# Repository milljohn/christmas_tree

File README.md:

# LED Christmas Tree

Give the gift of hacking. This is a great project to learn how to program or just enjoy the existing sketch.

## Background
I originally made this for my daughters when they were part of a community group for young entrepreneurs. The LED Christmas Tree was designed to be a product for them to build and sell. ThreeGirlsMakeStuff is now defunct.

## Programming

Supplies:
- [SparkFun ISP Pogo Adapter](https://www.sparkfun.com/products/11591)
- [USB Tiny AVR](https://www.aliexpress.com/item/1005003257284683.html?spm=a2g0o.productlist.0.0.764f665euosCDP&algo_pvid=e8b9d653-d5cf-4580-b718-6405428d7faf&algo_exp_id=e8b9d653-d5cf-4580-b718-6405428d7faf-10&pdp_ext_f=%7B%22sku_id%22%3A%2212000024884249441%22%7D)

The easiest thing to do is solder the Tiny AVR to the ISP Pogo Adapter.

- Click on File>Preferences 
- Add this to Additional Boards Manager URLs: ``https://raw.githubusercontent.com/damellis/attiny/ide-1.6.x-boards-manager/package_damellis_attiny_index.json`` 
- Click on Tools>Board>Board Manager
- Search for `attiny85` and install 
- Select ``ATtiny85``, ``Internal 8MHz``
- Click on Sketch>Include Library>Library Manager
- Search for Neopixel 

You can use any of the NeoPixel example sketches. Use the following configuration.

````c
#include <Adafruit_NeoPixel.h>
#ifdef __AVR__
  #include <avr/power.h>
#endif

#define PIN 0
#define NUM_LEDS 10
#define BRIGHTNESS 15

Adafruit_NeoPixel strip = Adafruit_NeoPixel(NUM_LEDS, PIN, NEO_GRB + NEO_KHZ800);
```

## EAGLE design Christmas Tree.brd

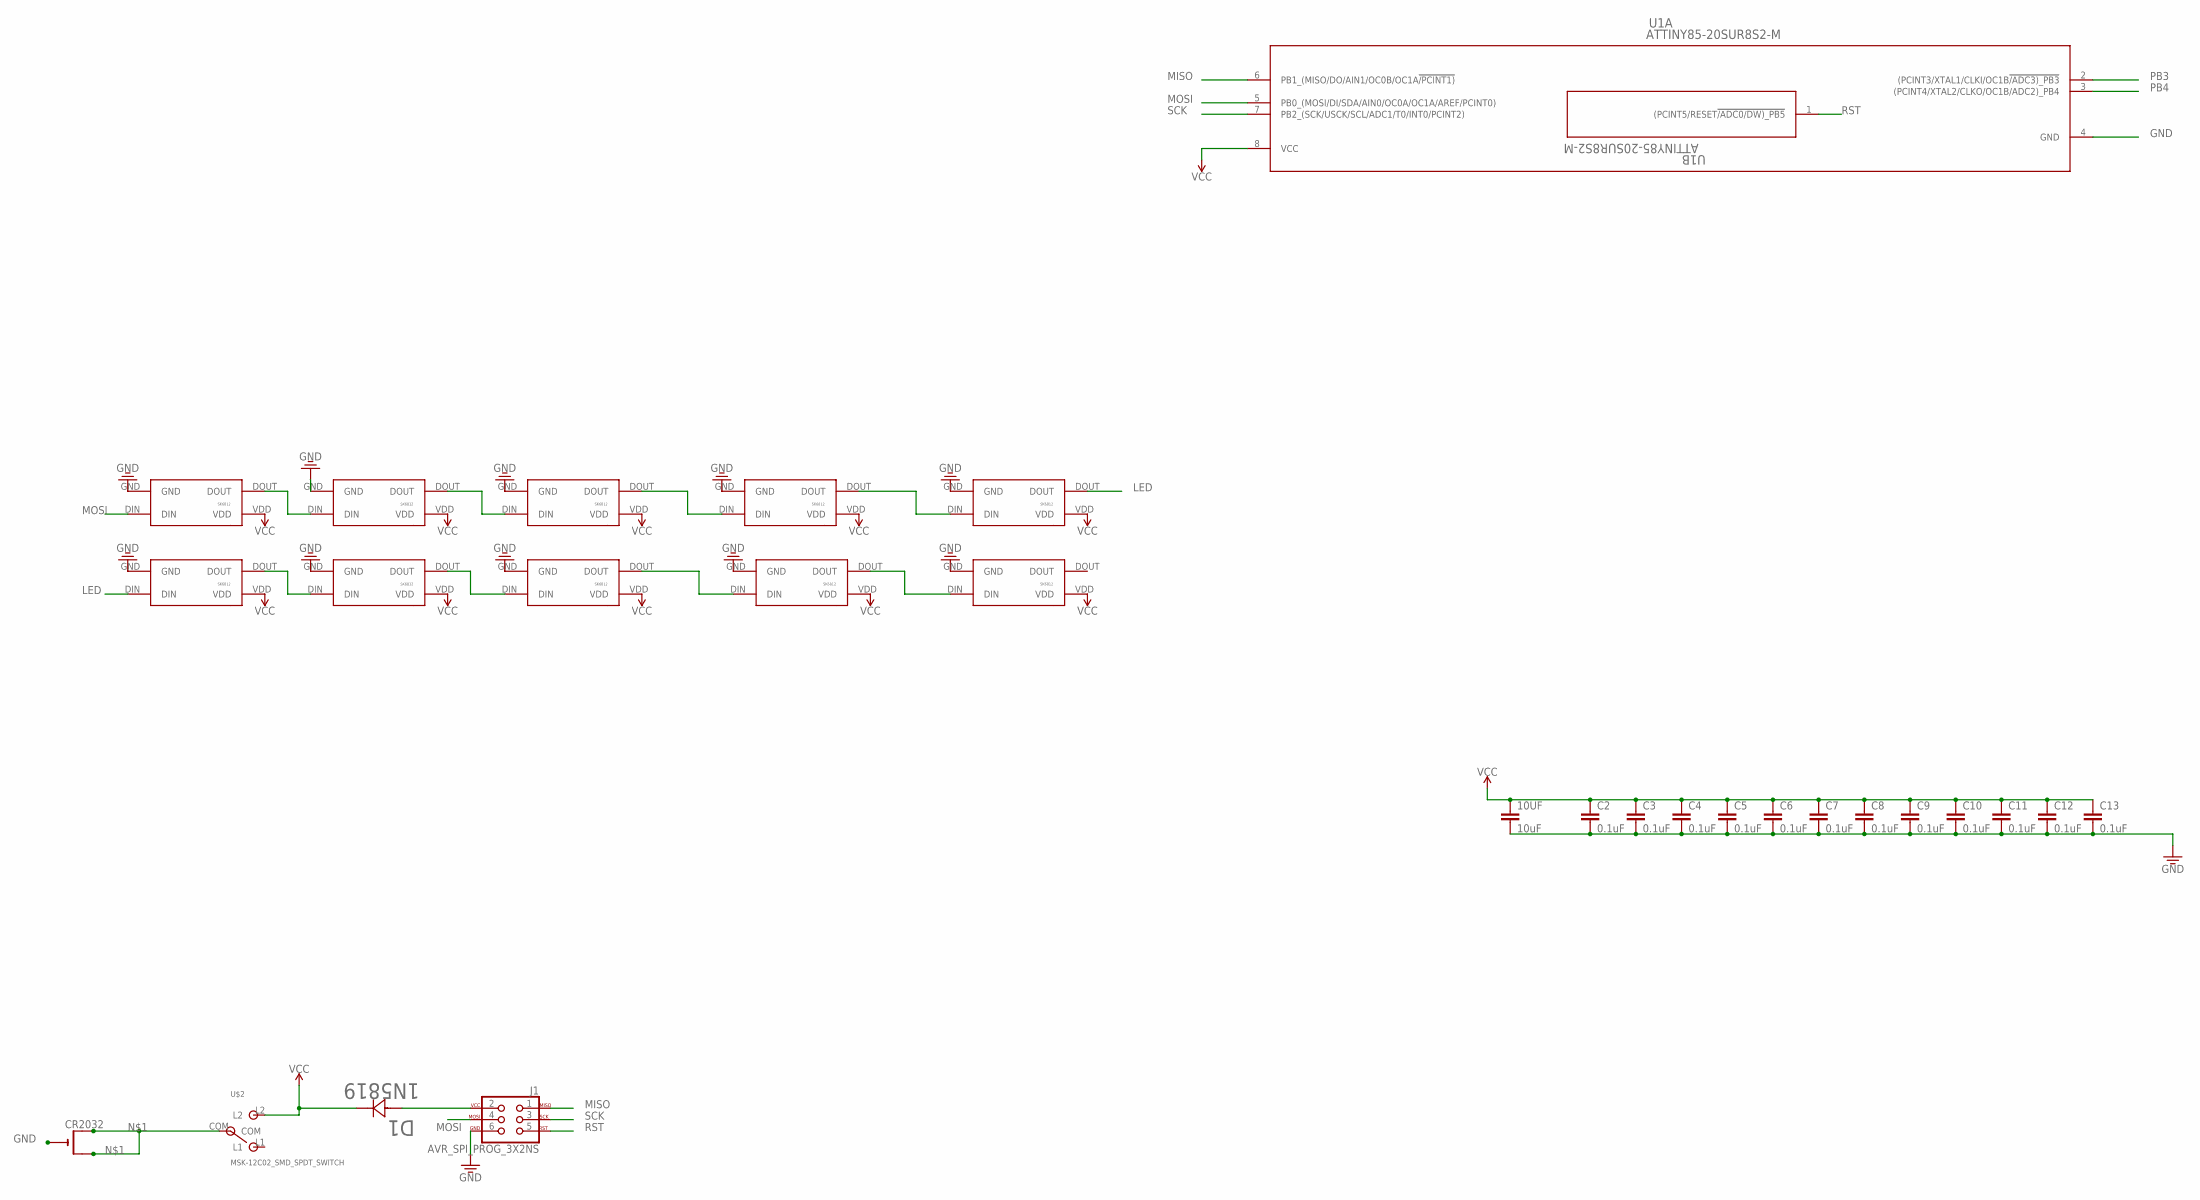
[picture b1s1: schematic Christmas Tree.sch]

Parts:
10UF: 10uF; 0805
C2, C3, C4, C5, C6, C7, C8, C9, C10, C11, C12, C13: 0.1uF; 0805
CR2032: CR2032SMT; CR2032-SMD
D1: 1N5819; SOD123-M
J1: AVR_SPI_PROG_3X2NS; 2X3-NS
U1: ATTINY85-20SUR8S2-M; 8S2-M
U$2: MSK-12C02_SMD_SPDT_SWITCH; MSK-12C02
U$3, U$4, U$5, U$6, U$7, U$8, U$9, U$10, U$11, U$12: SK6812; 5050

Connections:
GND: 10UF.2, C2.2, C3.2, C4.2, C5.2, C6.2, C7.2, C8.2, C9.2, C10.2, C11.2, C12.2, C13.2, CR2032.-, J1.6, U1.4 (GND), U$3.GND, U$4.GND, U$5.GND, U$6.GND, U$7.GND, U$8.GND, U$9.GND, U$10.GND, U$11.GND, U$12.GND
LED: U$7.DOUT, U$8.DIN
MISO: J1.1, U1.6 (PB1_(MISO/DO/AIN1/OC0B/OC1A!/PCINT1))
MOSI: J1.4, U1.5 (PB0_(MOSI/DI/SDA/AIN0/OC0A/OC1A/AREF/PC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), U$3.DIN
unnamed: CR2032.+$1 (+), CR2032.+$2 (+1), U$2.COM
unnamed: U$4.DOUT, U$5.DIN
unnamed: U$5.DOUT, U$6.DIN
unnamed: U$6.DOUT, U$7.DIN
unnamed: U$9.DOUT, U$10.DIN
unnamed: U$8.DOUT, U$9.DIN
unnamed: U$10.DOUT, U$11.DIN
unnamed: U$11.DOUT, U$12.DIN
unnamed: U$3.DOUT, U$4.DIN
unnamed: D1.2 (21), J1.2
PB3: U1.2 ((PCINT3/XTAL1/CLKI/OC1B!/ADC3)_PB3)
PB4: U1.3 ((PCINT4/XTAL2/CLKO/OC1B/ADC2)_PB4)
RST: J1.5, U1.1 ((PCINT5/RESET!/ADC0/DW)_PB5)
SCK: J1.3, U1.7 (PB2_(SCK/USCK/SCL/ADC1/T0/INT0/PCINT2))
VCC: 10UF.1, C2.1, C3.1, C4.1, C5.1, C6.1, C7.1, C8.1, C9.1, C10.1, C11.1, C12.1, C13.1, D1.1 (12), U1.8 (VCC), U$2.L2, U$3.VDD, U$4.VDD, U$5.VDD, U$6.VDD, U$7.VDD, U$8.VDD, U$9.VDD, U$10.VDD, U$11.VDD, U$12.VDD

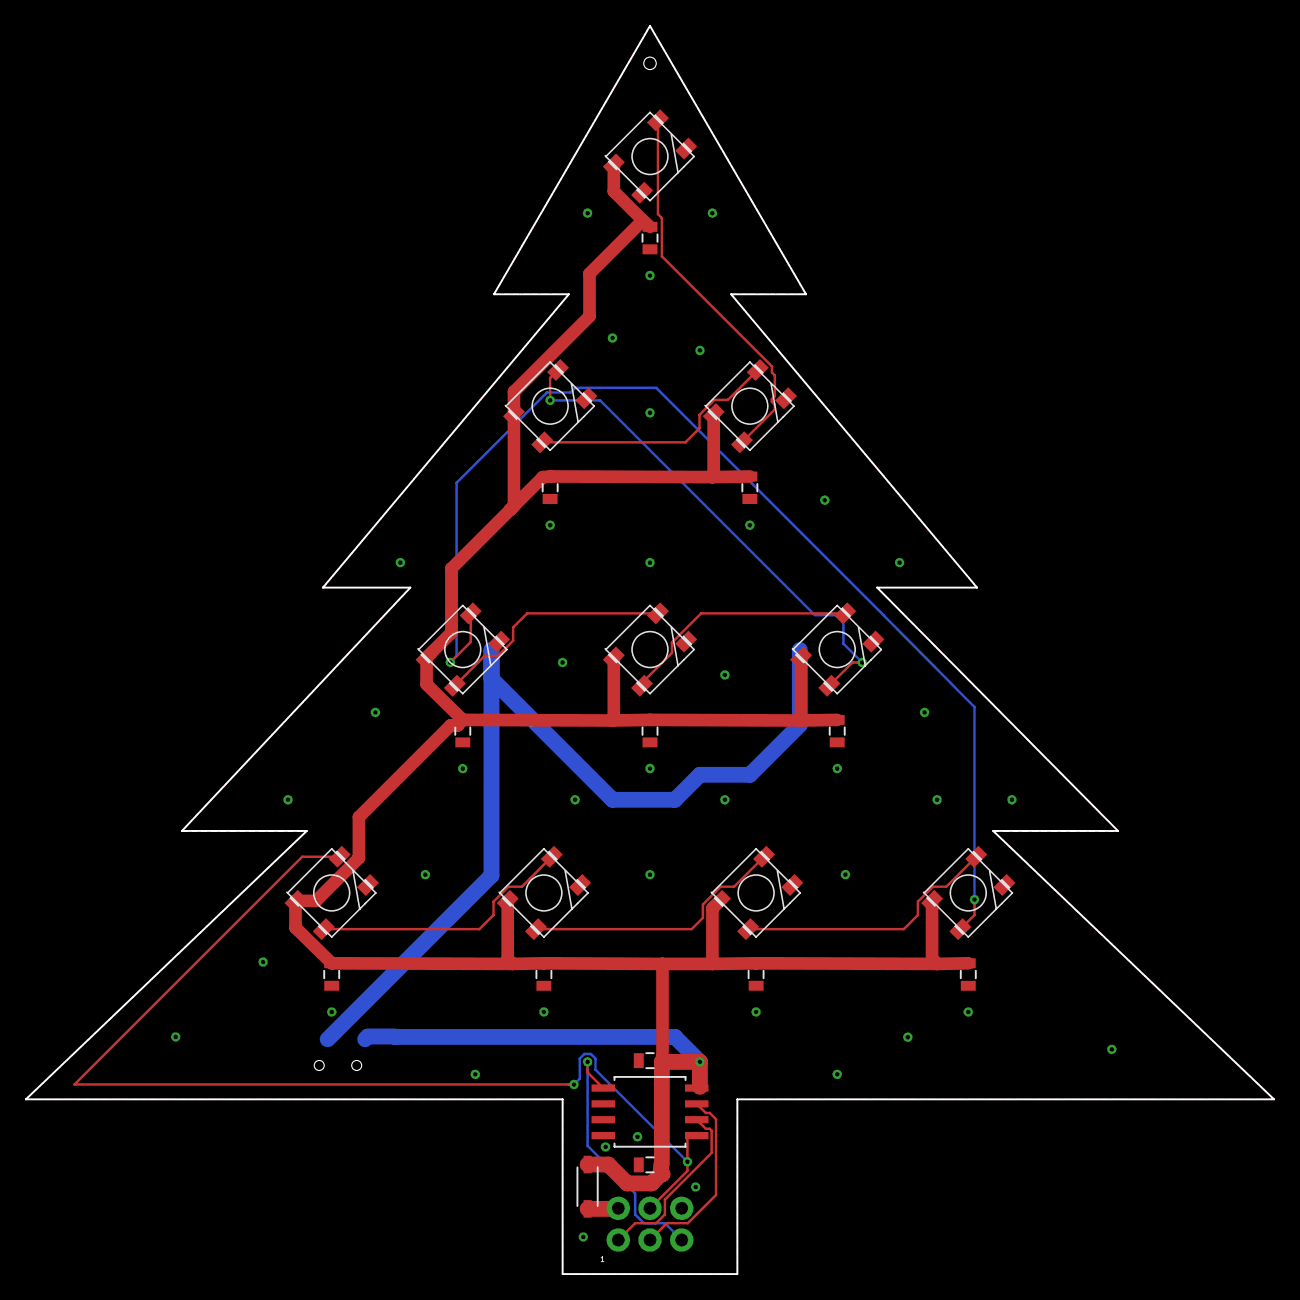
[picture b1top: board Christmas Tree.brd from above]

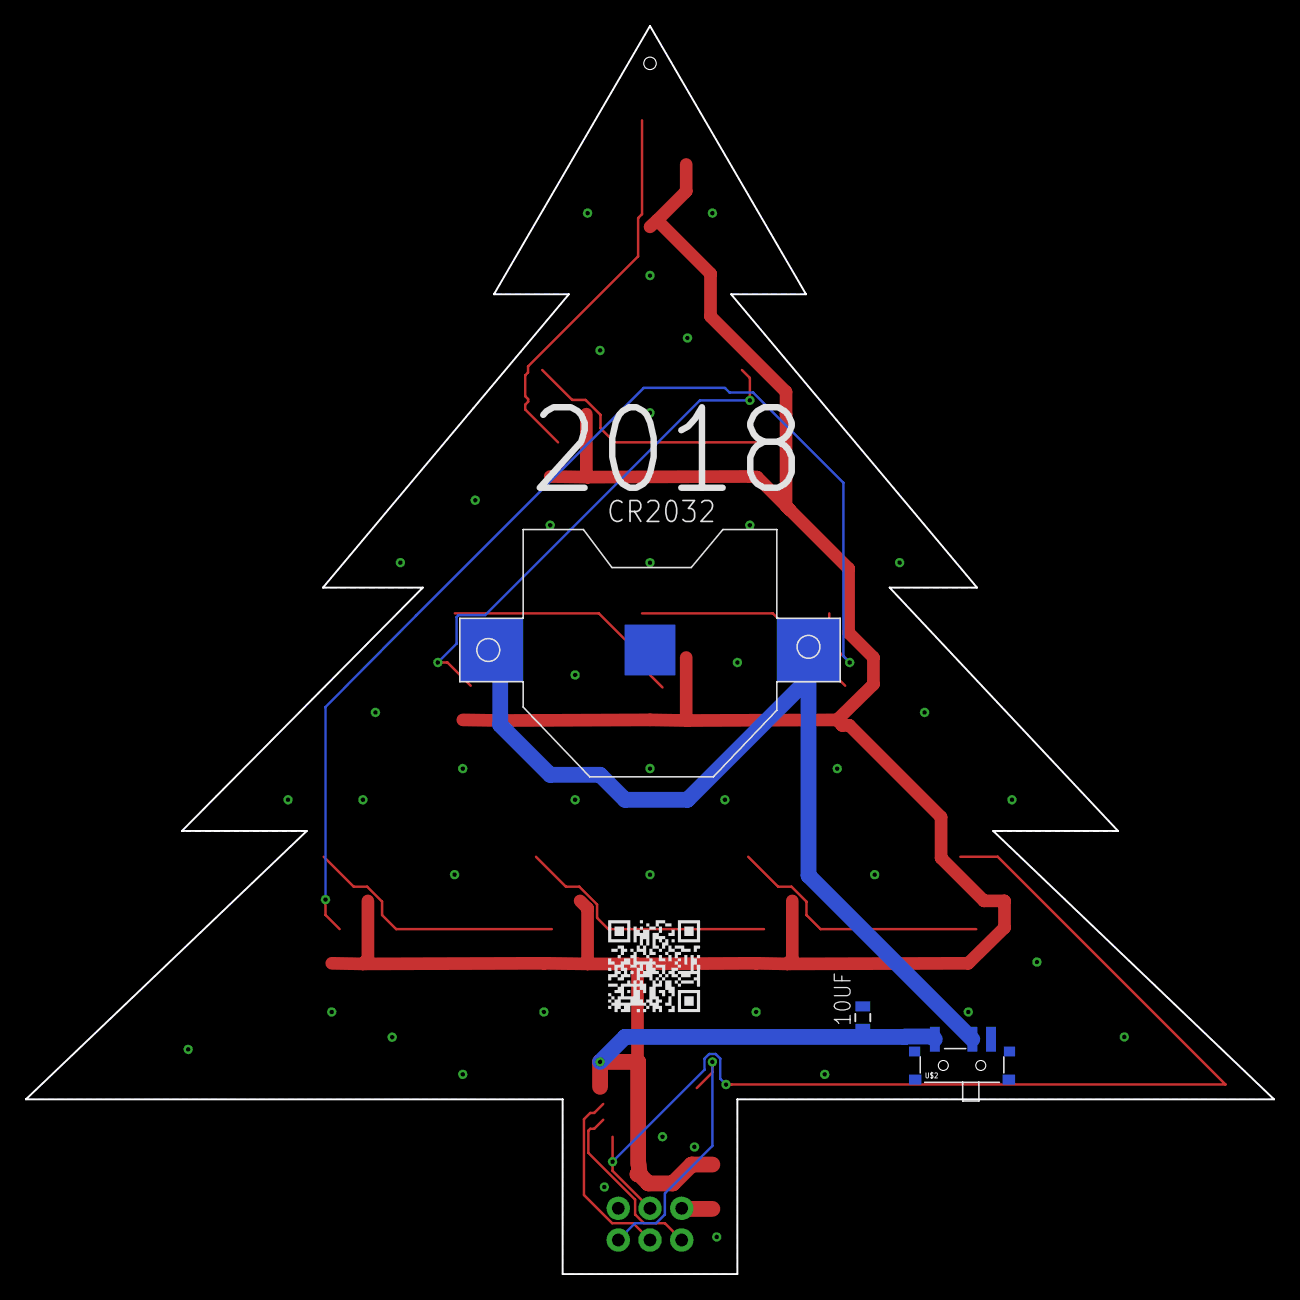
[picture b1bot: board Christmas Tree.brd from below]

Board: 2 copper layers, 100.0 x 100.0 mm, 29 parts (3 on the bottom side), 17 nets.

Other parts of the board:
U$1: XMASTREE

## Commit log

2021-12-18 move attiny on schematic

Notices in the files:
parts and their libraries:
SparkFun-Connectors: Licensing: Creative Commons ShareAlike 4.0 International - https://creativecommons.org/licenses/by-sa/4.0
